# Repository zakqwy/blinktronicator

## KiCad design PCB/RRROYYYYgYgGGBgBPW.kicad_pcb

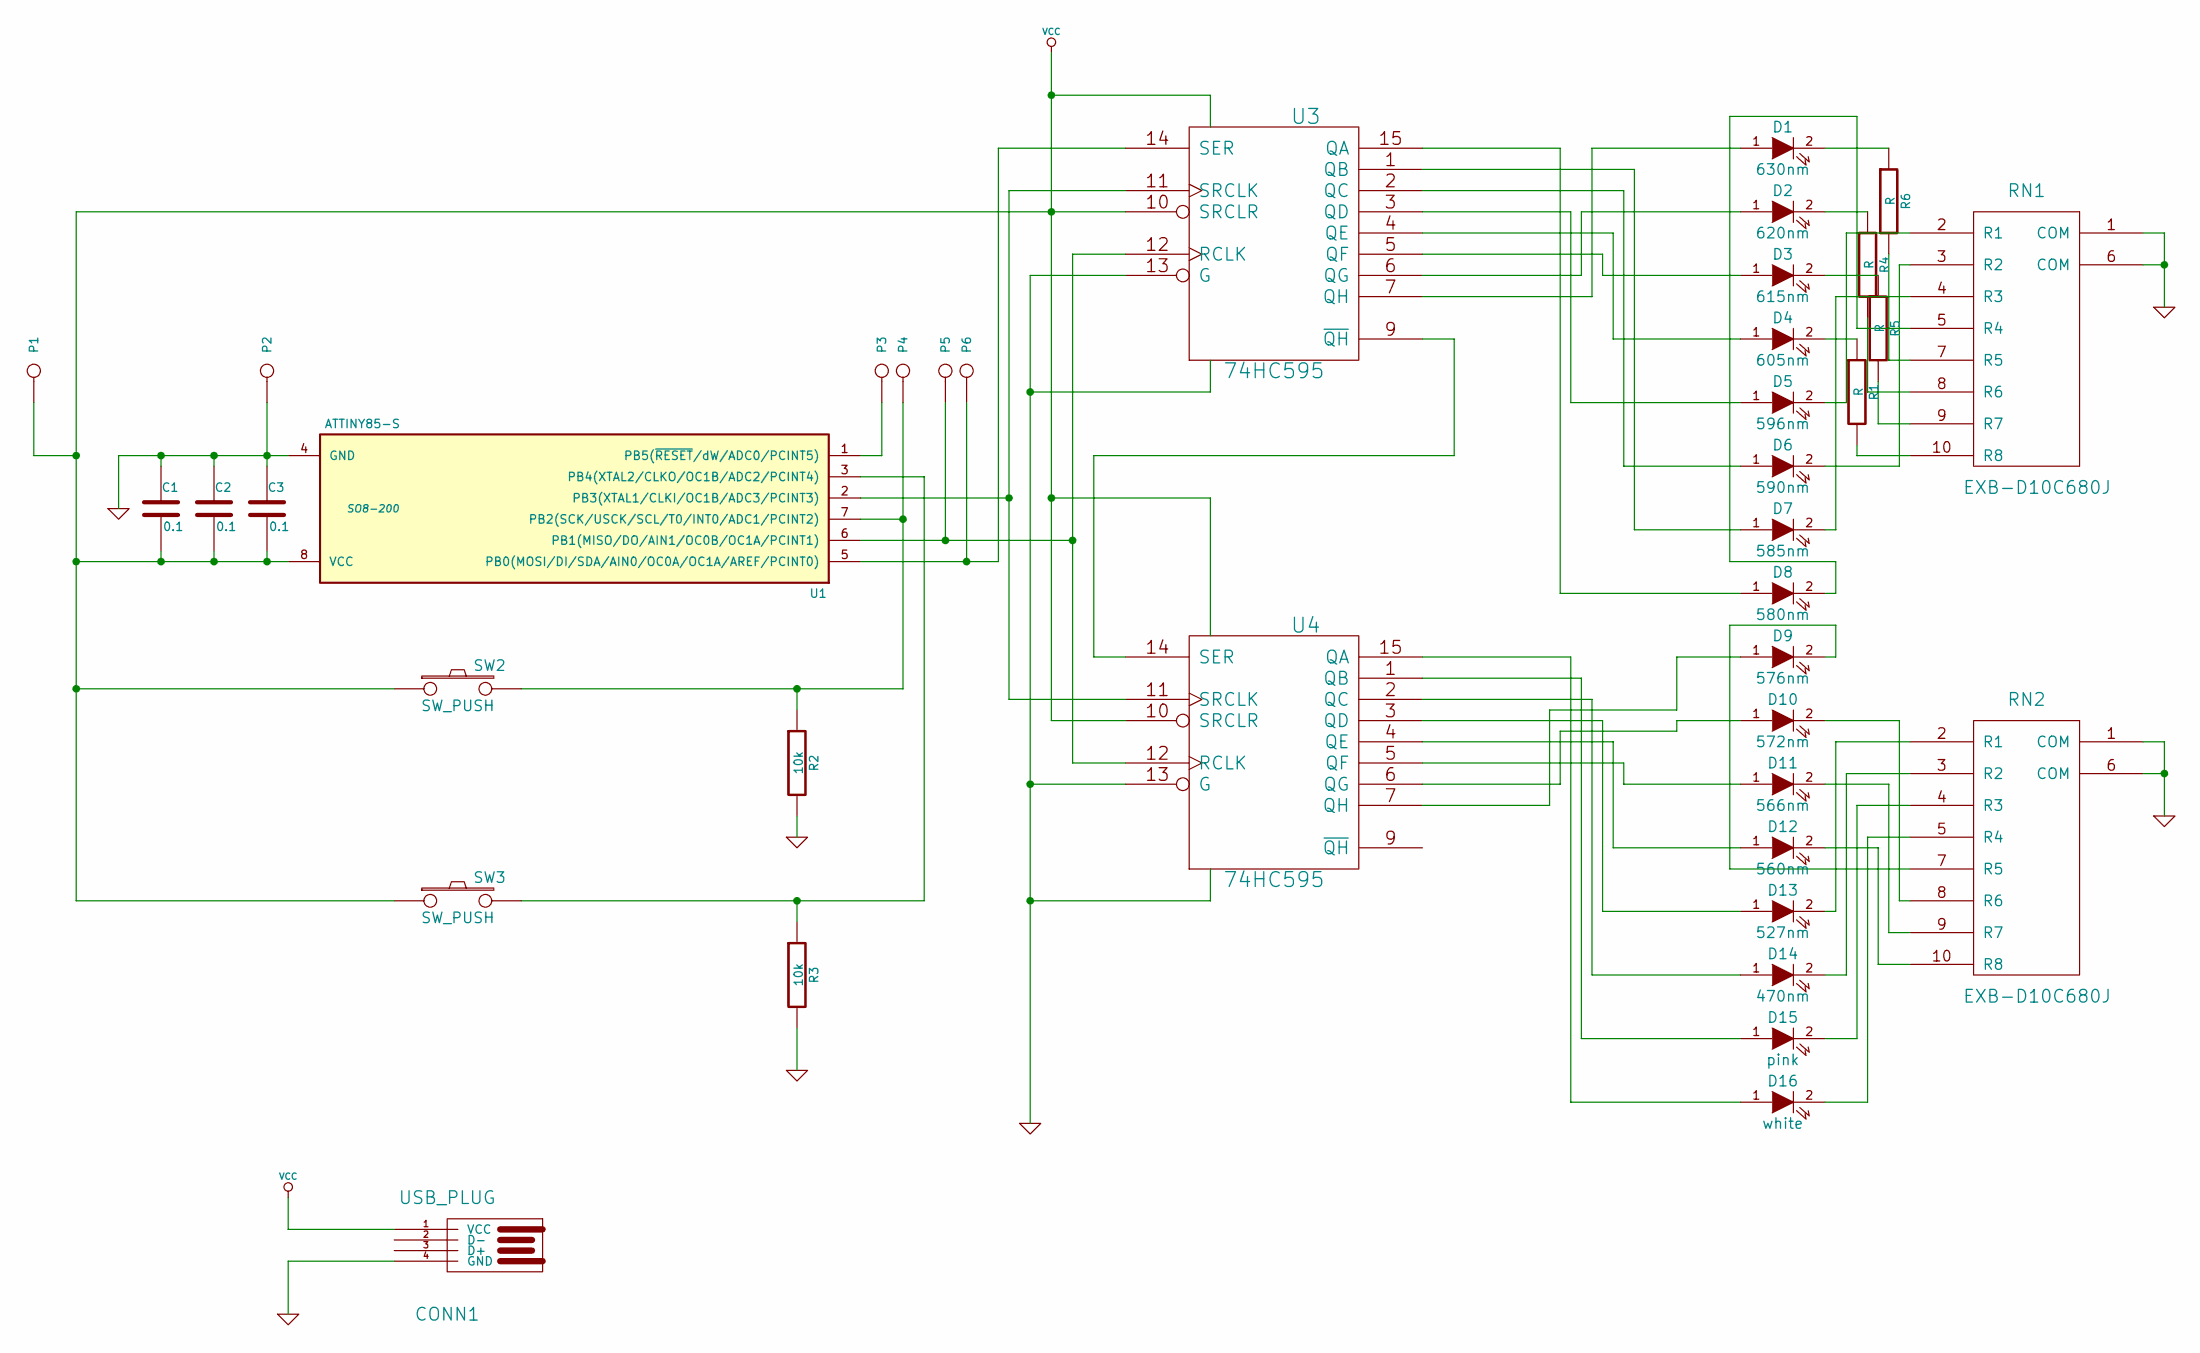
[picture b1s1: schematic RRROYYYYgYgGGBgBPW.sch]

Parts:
C1, C2, C3: 0.1
CONN1: USB_PLUG
D1: 630nm
D2: 620nm
D3: 615nm
D4: 605nm
D5: 596nm
D6: 590nm
D7: 585nm
D8: 580nm
D9: 576nm
D10: 572nm
D11: 566nm
D12: 560nm
D13: 527nm
D14: 470nm
D15: pink
D16: white
P1: VCC
P2: GND
P3: RST
P4: SCK
P5: MISO
P6: MOSI
R1, R4, R5, R6: R
R2, R3: 10k
RN1, RN2: EXB-D10C680J
SW2, SW3: SW_PUSH
U1: ATTINY85-S; SO8-200
U3, U4: 74HC595

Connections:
GND: C1.1, C2.1, C3.1, CONN1.4 (GND), P2.1, R2.2, R3.2, RN1.1 (COM), RN1.6 (COM), RN2.1 (COM), RN2.6 (COM), U1.4 (GND), U3.8 (GND), U3.13 (G), U4.8 (GND), U4.13 (G)
unnamed: D3.1 (A), U3.5 (QF)
unnamed: D2.1 (A), U3.6 (QG)
unnamed: D1.1 (A), U3.7 (QH)
unnamed: U3.9 (~QH), U4.14 (SER)
unnamed: D4.2 (K), R1.1
unnamed: R1.2, RN1.10 (R8)
unnamed: R5.2, RN1.9 (R7)
unnamed: D3.2 (K), R5.1
unnamed: R4.2, RN1.8 (R6)
unnamed: D2.2 (K), R4.1
unnamed: D1.2 (K), R6.1
unnamed: D5.2 (K), RN1.2 (R1)
unnamed: P5.1, U1.6 (PB1(MISO/DO/AIN1/OC0B/OC1A/PCINT1)), U3.12 (RCLK), U4.12 (RCLK)
unnamed: P4.1, R2.1, SW2.2, U1.7 (PB2(SCK/USCK/SCL/T0/INT0/ADC1/PCINT2))
unnamed: P3.1, U1.1 (PB5(~RESET~/dW/ADC0/PCINT5))
unnamed: U1.2 (PB3(XTAL1/CLKI/OC1B/ADC3/PCINT3)), U3.11 (SRCLK), U4.11 (SRCLK)
unnamed: R3.1, SW3.2, U1.3 (PB4(XTAL2/CLKO/OC1B/ADC2/PCINT4))
unnamed: D9.1 (A), U4.7 (QH)
unnamed: R6.2, RN1.7 (R5)
unnamed: D15.2 (K), RN2.4 (R3)
unnamed: D16.2 (K), RN2.5 (R4)
unnamed: P6.1, U1.5 (PB0(MOSI/DI/SDA/AIN0/OC0A/OC1A/AREF/PCI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), U3.14 (SER)
unnamed: D15.1 (A), U4.1 (QB)
unnamed: D16.1 (A), U4.15 (QA)
unnamed: D8.1 (A), U3.15 (QA)
unnamed: D7.1 (A), U3.1 (QB)
unnamed: D6.1 (A), U3.2 (QC)
unnamed: D5.1 (A), U3.3 (QD)
unnamed: D4.1 (A), U3.4 (QE)
unnamed: D10.1 (A), U4.6 (QG)
unnamed: D11.1 (A), U4.5 (QF)
unnamed: D12.1 (A), U4.4 (QE)
unnamed: D13.1 (A), U4.3 (QD)
unnamed: D14.1 (A), U4.2 (QC)
unnamed: D14.2 (K), RN2.3 (R2)
unnamed: D6.2 (K), RN1.3 (R2)
unnamed: D12.2 (K), RN2.10 (R8)
unnamed: D11.2 (K), RN2.9 (R7)
unnamed: D10.2 (K), RN2.8 (R6)
unnamed: D9.2 (K), RN2.7 (R5)
unnamed: D7.2 (K), RN1.4 (R3)
unnamed: D8.2 (K), RN1.5 (R4)
unnamed: D13.2 (K), RN2.2 (R1)
VCC: C1.2, C2.2, C3.2, CONN1.1 (VCC), P1.1, SW2.1, SW3.1, U1.8 (VCC), U3.10 (SRCLR), U3.16 (VCC), U4.10 (SRCLR), U4.16 (VCC)

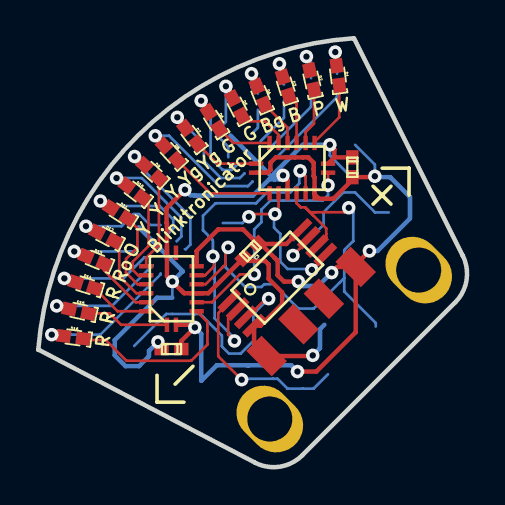
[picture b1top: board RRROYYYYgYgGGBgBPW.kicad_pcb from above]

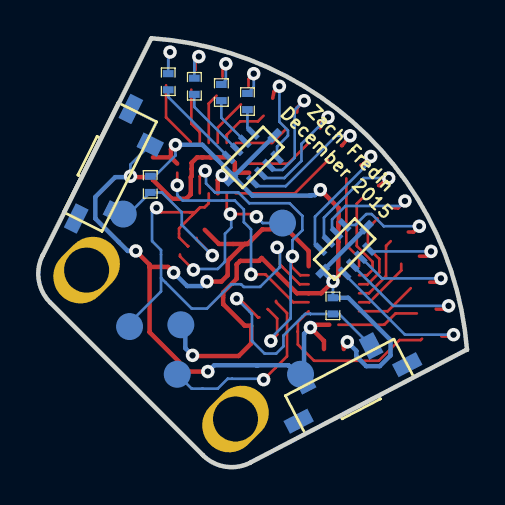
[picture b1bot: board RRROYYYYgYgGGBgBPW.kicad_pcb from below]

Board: 2 copper layers, 23.8 x 23.8 mm, 39 parts (16 on the bottom side), 45 nets.

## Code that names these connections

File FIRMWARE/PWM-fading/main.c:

/*
Blinktronicator

MIT License (MIT)
Copyright (c) 2015 Zach Fredin

Permission is hereby granted, free of charge, to any person obtaining a copy of this software and associated documentation files (the "Software"), to deal in the Software without restriction, including without limitation the rights to use, copy, modify, merge, publish, distribute, sublicense, and/or sell copies of the Software, and to permit persons to whom the Software is furnished to do so, subject to the following conditions:

The above copyright notice and this permission notice shall be included in all copies or substantial portions of the Software.

THE SOFTWARE IS PROVIDED "AS IS", WITHOUT WARRANTY OF ANY KIND, EXPRESS OR IMPLIED, INCLUDING BUT NOT LIMITED TO THE WARRANTIES OF MERCHANTABILITY, FITNESS FOR A PARTICULAR PURPOSE AND NONINFRINGEMENT. IN NO EVENT SHALL THE AUTHORS OR COPYRIGHT HOLDERS BE LIABLE FOR ANY CLAIM, DAMAGES OR OTHER LIABILITY, WHETHER IN AN ACTION OF CONTRACT, TORT OR OTHERWISE, ARISING FROM, OUT OF OR IN CONNECTION WITH THE SOFTWARE OR THE USE OR OTHER DEALINGS IN THE SOFTWARE.

more info: https://hackaday.io/project/8331-blinktronicator
*/

#include <avr/io.h>
#include <avr/interrupt.h>

/* Shift register pin definitions */
#define PIN_DATA 0	//14 DS			ATtiny45 pin 5, PB0 	schematic name PIN_SER
#define PIN_CLOCK 3 	//11 SHCP		ATtiny45 pin 2, PB3 	schematic name PIN_SRCLK
//	PIN_MR [H] 	//10 master reset	connected to VCC	schematic name PIN_SRCLR
#define PIN_LATCH 1  	//12 STCP		ATtiny45 pin 6, PB1	schematic name PIN_RCLK
//	PIN_OE [L]	//13 output enable	connected to GND	schematic name PIN_G

/* Testing pins */
#define PIN_MISO 1 	//ATtiny45 pin 6, PB1
#define PIN_MOSI 0	//ATtiny45 pin 5, PB0

/* Switch pins */
#define SW_LEFT 4	//ATtiny45 pin 3, PB4
#define SW_RIGHT 2	//ATtiny45 pin 7, PB2	

/* Global variables */
uint8_t faderCount = 0; //used for iterating through displayFader() [for PWM generation]
uint8_t valueLEDs[16] = {20,28,34,40,44,48,52,56,60,63,66,69,72,74,77,80}; //values from 0 to 255 for LEDs, L to R (starting with 630nm)

unsigned char currentLEDstate1 = 0;
unsigned char currentLEDstate2 = 0;

void SystemInit(void) {
/* Port B configuration */
	DDRB |= ((1 << PIN_DATA) + (1 << PIN_CLOCK) + (1 << PIN_LATCH));//sets three I/O pins as outputs to send signals to 74HC595
									//note that MISO is an output for testing (set via PIN_RCLK)
	PORTB = 0;	
}

void updateLEDs(unsigned char ledOutput1, unsigned char ledOutput2) {
	/* this could probably be more efficient. the second it started working, I saved the function and moved on. */

	int i;
	PORTB &= ~(1<<PIN_LATCH); //starts by clearing latch pin	


	for (i = 7; i >= 0; i--) { //first eight bits...
		if (ledOutput1 & (1<<i)) { //runs through the eight bits that make up ledOutput1
			PORTB |= (1<<PIN_DATA); //sets data pin if it should be high
		}


		PORTB |= (1<<PIN_CLOCK); //sets clock pin (after data pin!)
		PORTB &= ~((1<<PIN_DATA) + (1<<PIN_CLOCK)); //clears data pin regardless of its status. also clears clock pin.
	}

	for (i = 7; i >= 0; i--) {	
		if (ledOutput2 & (1<<i)) {
			PORTB |= (1<<PIN_DATA);
		}
		PORTB |= (1<<PIN_CLOCK);
		PORTB &= ~((1<<PIN_DATA) + (1<<PIN_CLOCK));
	}

	PORTB |= (1<<PIN_LATCH); //sets latch pin to update display
	PORTB &= ~(1<<PIN_LATCH);
}

void displayFader() {
// 8-bit PWM fader for LEDs
// uses global variable values to determine whether or not to turn various LEDs on or off

/* 	global varibales used
		faderCount (uint8_t)	
		valueLEDs[16] (uint8_t)
*/

	int counter; // which LED are we on? 

	currentLEDstate1 = 0;
	currentLEDstate2 = 0;

	for (counter = 0; counter <=7; counter++) { // cycle through both LED arrays

		if (valueLEDs[counter] > faderCount) {
			currentLEDstate1 |= (1<<counter);	
		}

		if (valueLEDs[counter + 8] > faderCount) {
			currentLEDstate2 |= (1<<counter);
		}

	}
	if (faderCount <= 100) {
		faderCount += 1;
	}
	else {
		faderCount = 0;
	}
}

int main(void) {
	SystemInit();

	long slowLoop = 0;
	long slowLoopOverflow = 500; //5000: speedy but visible


	int buttonLeft = 0;
	int buttonRight = 0;

	int counter = 0;

	for(;;) {

			if (slowLoop == slowLoopOverflow) {
			
			/*	demo routine to fade across LEDs	*/		
				for (counter = 0; counter <= 15; counter++) { //cycle through LEDs
					valueLEDs[counter] += 1;				
					if (valueLEDs[counter] > 20) {
						valueLEDs[counter] = 1;
					}
				}
			
				slowLoop = 0;
			}
		

			displayFader();
			updateLEDs(currentLEDstate1, currentLEDstate2);
			slowLoop += 1;
	
	}
}

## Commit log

2015-11-06 Changed from buck to boost converter for 3vdc power. Added values and designators for various components. Generated a netlist. More changes (likely) to come.
2015-11-08 added pink and white LEDs. started pcb layout. LEDs arranged in an ~80 degree arc. schematic changed around a bit to make routing a tiny bit easier. note: schematic (specifically around shift registe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
2015-11-09 moved a bunch of traces around and slightly reduced the rats nest.
2015-11-10 changed the file names to reflect addition of pink and white LEDs. finished routing, beefed up power rails, rounded corners. changed processor footprint to TSSOP. still needs a thorough review...
2015-12-08 changed from 3.3vdc boost converter + 2032 coin cell to usb plug power. added silkscreen, re-routed, etc. resistor network value still TBD, i'm afraid (it worked at 3.3vdc, but might not here...)
2015-12-08 realized the resistor networks were sized for 3.3vdc power; moving to 5vdc power means the shorter wavelength stuff needs a different value. bodged in a quartet of 0402 resistors, mounted on the back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
2015-12-08 removed a few reference marks
2015-12-28 many changes. formal name change from "RRRROOOGG..etc" to "blinktronicator". got basic functions working (led update function, mostly). updated PCB to eliminate stupid errors--mirror image shift regi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
2015-12-28 changed speed to reflect comment (50000 to 5000)
2015-12-31 Several minor PCB updates (slots for USB connector, changed silkscreen, etc).
2015-12-31 added license file (again)...
2016-01-02 Added a PWM fading function along with some demo code.
2016-06-12 Broke program into three groups: a simple PWM fading routine, the old runtime program, and the new version with four operating modes. FIRMWARE/runtime is now the standard blinktronicator program.
